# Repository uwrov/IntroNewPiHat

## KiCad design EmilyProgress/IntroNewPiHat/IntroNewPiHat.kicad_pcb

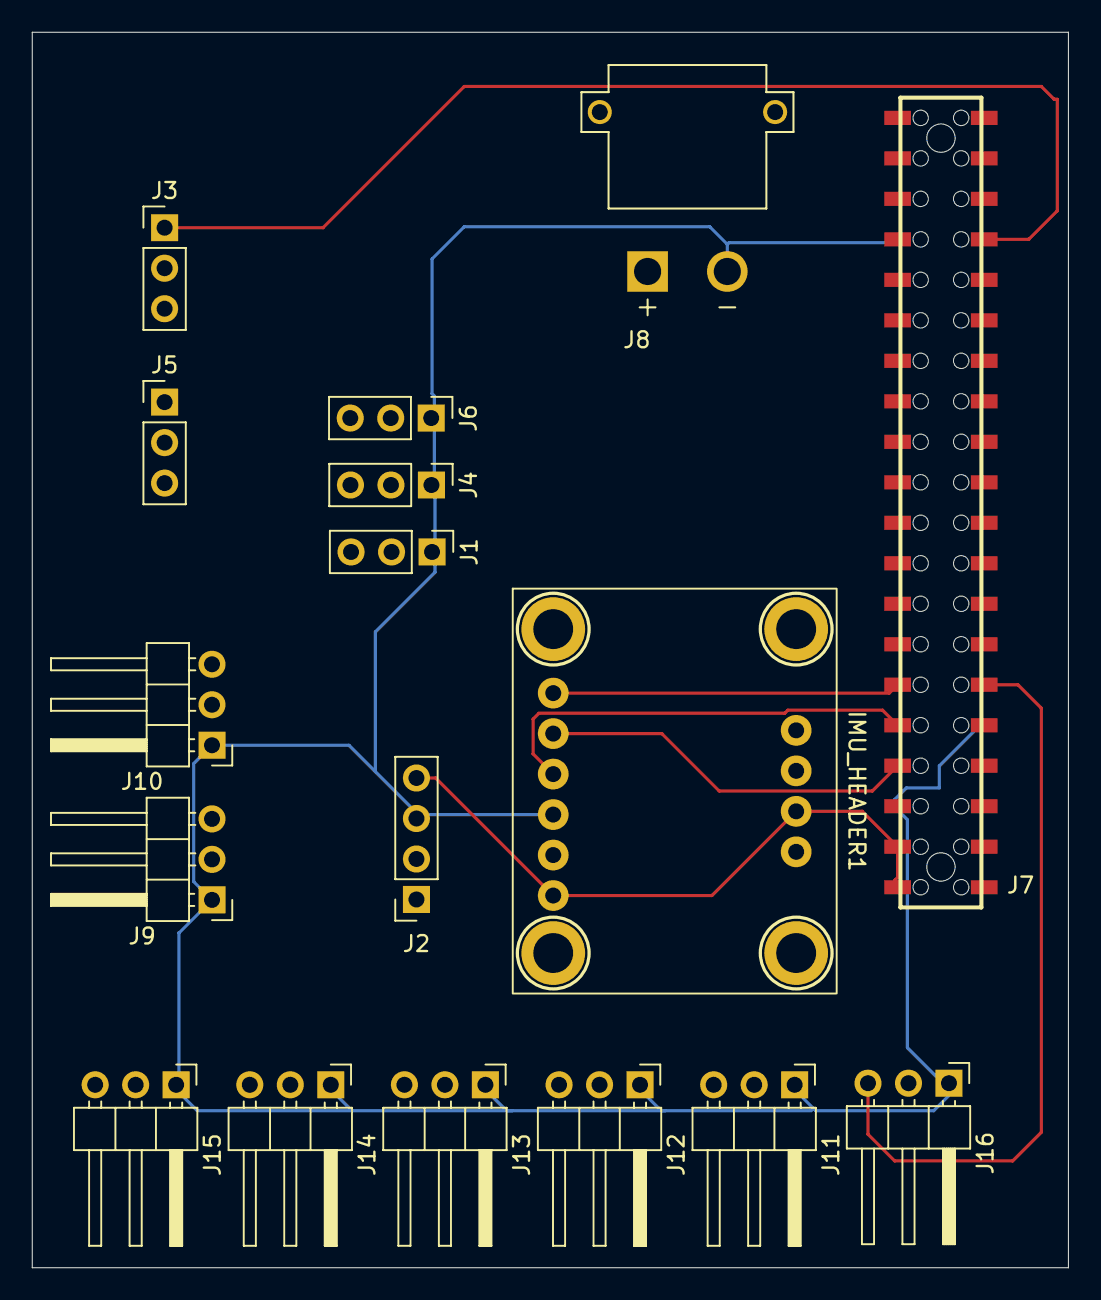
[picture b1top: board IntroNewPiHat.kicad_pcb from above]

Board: 2 copper layers, 65.0 x 77.5 mm, 17 parts (0 on the bottom side), 21 nets.

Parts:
IMU_HEADER1: HEADER-1X6; Adafruit_BPO055
J1, J3, J4, J5, J6: Conn_01x03_Pin; PinHeader_1x03_P2.54mm_Vertical
J2: Conn_01x04_Pin; PinSocket_1x04_P2.54mm_Vertical
J7: RPi_GPIO; Samtec_HLE-120-02-XXX-DV-BE-XX-XX
J8: XT30PW-M; AMASS_XT30PW-M
J9, J10, J11, J12, J13, J14, J15, J16: Conn_01x03_Pin; PinHeader_1x03_P2.54mm_Horizontal

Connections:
/3.3VPWR: J1.2, J4.2, J6.2, J7.1 (3.3V), J7.17 (3.3V)
/B36: J7.36 (BCM16), J15.3
/E37: J7.37 (BCM26), J13.3
/GND: IMU_HEADER1.4, J1.1, J2.1, J4.1, J6.1, J7.6 (GND), J7.9 (GND), J7.34 (GND), J8.N, J9.1, J10.1, J11.1, J12.1, J13.1, J14.1, J15.1, J16.1
/PIN5: J7.29 (BCM5), J14.3
/PIN17: J7.11 (BCM17), J16.3
/PWM0: J5.1, J7.32 (BCM12_PWM0)
/PWM1: J3.1, J7.33 (BCM13_PWM1)
/PWM2: J1.3, J7.16 (BCM23)
/PWM3: J4.3, J7.18 (BCM24)
/PWM4: J6.3, J7.22 (BCM25)
/PWR: IMU_HEADER1.3, IMU_HEADER1.6, J2.4, J7.2 (5V), J7.4 (5V), J8.P
/RST: IMU_HEADER1.1, J7.12 (BCM18_PCM_C)
/RX10: IMU_HEADER1.3, J7.10 (BCM15_RXD)
/S119: J7.19 (BCM10_MOSI), J9.3
/S221: J7.21 (BCM9_MISO), J10.3
/S323: J7.23 (BCM11_SCLK), J11.3
/S431: J7.31 (BCM6), J12.3
/SCL: J2.3, J7.5 (BCM3_SCL)
/SDA: J2.2, J7.3 (BCM2_SDA)
/TX08: IMU_HEADER1.2, J7.8 (BCM14_TXD)

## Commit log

2024-11-10 Emily's progress
2024-11-17 added more stuff to pihat - 11/17
2024-11-25 11/24 update
2024-12-02 update 12/1/2024
